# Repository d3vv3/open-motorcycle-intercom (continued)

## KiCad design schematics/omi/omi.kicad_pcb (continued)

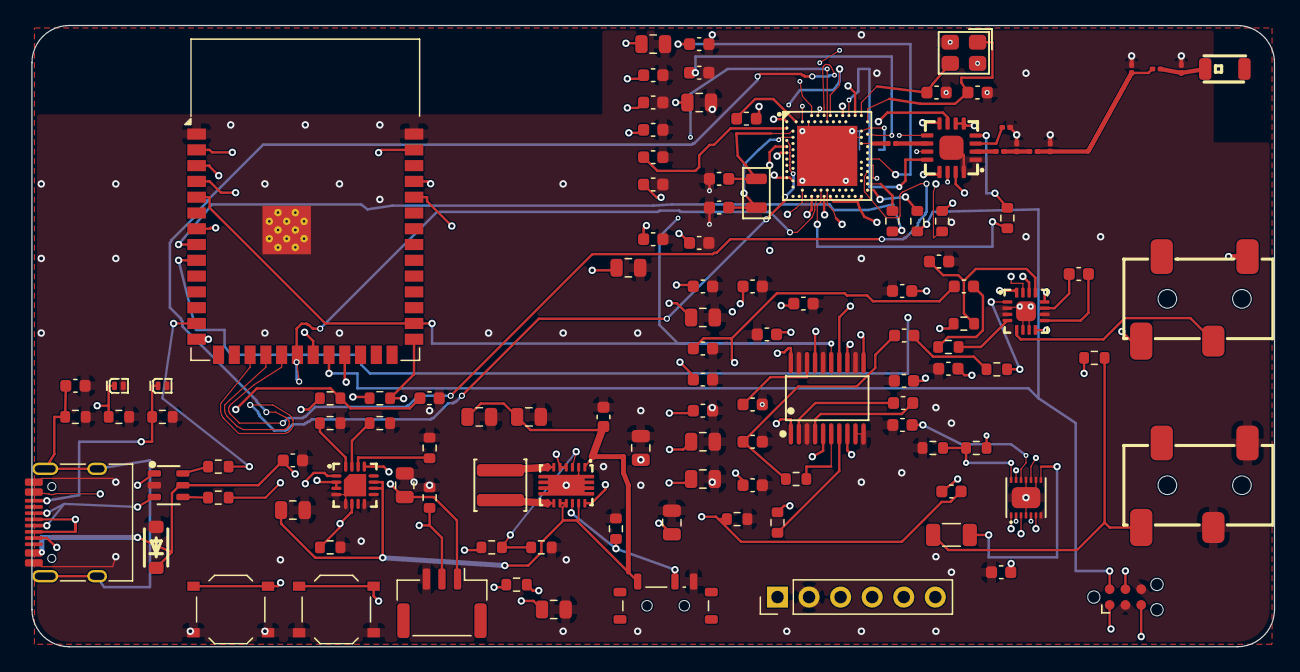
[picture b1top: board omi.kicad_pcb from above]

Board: 4 copper layers, 100.0 x 50.0 mm, 117 parts (1 on the bottom side), 99 nets.

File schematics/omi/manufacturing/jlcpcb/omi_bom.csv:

"Designator","Comment","Footprint","LCSC"
"AE1","2450AT18A100E","JLC-MCP:ANT-SMD_L3.2-W1.6","C89334"
"C23","4.7uF","Capacitor_SMD:C_0805_2012Metric","C76639"
"C24","100nF","Capacitor_SMD:C_0603_1608Metric","C108079"
"C25","100nF","Capacitor_SMD:C_0603_1608Metric","C108079"
"C26","100nF","Capacitor_SMD:C_0603_1608Metric","C108079"
"C27","100nF DEC1","Capacitor_SMD:C_0603_1608Metric","C108079"
"C28","100nF DEC2","Capacitor_SMD:C_0603_1608Metric","C108079"
"C29","100pF DEC3","Capacitor_SMD:C_0603_1608Metric","C14665"
"C30","1uF DEC4","Capacitor_SMD:C_0603_1608Metric","C113807"
"C31","1uF DEC5","Capacitor_SMD:C_0603_1608Metric","C113807"
"C32","1uF DEC6","Capacitor_SMD:C_0603_1608Metric","C113807"
"C33","4.7uF DECUSB","Capacitor_SMD:C_0805_2012Metric","C76639"
"C34","12pF","Capacitor_SMD:C_0603_1608Metric","C107034"
"C35","12pF","Capacitor_SMD:C_0603_1608Metric","C107034"
"C36","20pF","Capacitor_SMD:C_0603_1608Metric","C325469"
"C37","20pF","Capacitor_SMD:C_0603_1608Metric","C325469"
"C38","100nF","Capacitor_SMD:C_0603_1608Metric","C108079"
"C39","10uF","Capacitor_SMD:C_0805_2012Metric","C380331"
"C42","1uF","Capacitor_SMD:C_0603_1608Metric","C113807"
"C43","4.7uF","Capacitor_SMD:C_0805_2012Metric","C76639"
"C44","4.7uF","Capacitor_SMD:C_0805_2012Metric","C76639"
"C45","10uF 6.3V X5R","Capacitor_SMD:C_0805_2012Metric","C380331"
"C46","10uF 6.3V X5R","Capacitor_SMD:C_0805_2012Metric","C380331"
"C47","100nF","Capacitor_SMD:C_0603_1608Metric","C108079"
"C48","22uF 6.3V X5R","Capacitor_SMD:C_0805_2012Metric","C380336"
"C49","22uF 6.3V X5R","Capacitor_SMD:C_0805_2012Metric","C380336"
"C50","22uF 6.3V X5R","Capacitor_SMD:C_0805_2012Metric","C380336"
"C51","1uF","Capacitor_SMD:C_0603_1608Metric","C113807"
"C52","1.0pF C0G RF (Nordic ref)","Capacitor_SMD:C_0201_0603Metric","C85893"
"C53","2.0pF C0G RF (Nordic ref)","Capacitor_SMD:C_0201_0603Metric","C88875"
"C54","1.0pF C0G RF (Nordic ref)","Capacitor_SMD:C_0201_0603Metric","C85893"
"C55","100nF","Capacitor_SMD:C_0603_1608Metric","C108079"
"C56","10uF","Capacitor_SMD:C_0805_2012Metric","C380331"
"C57","100nF","Capacitor_SMD:C_0603_1608Metric","C108079"
"C58","10uF","Capacitor_SMD:C_0805_2012Metric","C380331"
"C59","100nF","Capacitor_SMD:C_0603_1608Metric","C108079"
"C60","10uF","Capacitor_SMD:C_0805_2012Metric","C380331"
"C61","2.2uF","Capacitor_SMD:C_0603_1608Metric","C513691"
"C62","2.2uF","Capacitor_SMD:C_0603_1608Metric","C513691"
"C63","100nF","Capacitor_SMD:C_0603_1608Metric","C108079"
"C64","2.2nF C0G","Capacitor_SMD:C_0603_1608Metric","C107043"
"C65","2.2nF C0G","Capacitor_SMD:C_0603_1608Metric","C107043"
"C66","1uF","Capacitor_SMD:C_0603_1608Metric","C113807"
"C67","1uF","Capacitor_SMD:C_0603_1608Metric","C113807"
"C68","1uF","Capacitor_SMD:C_0603_1608Metric","C113807"
"C69","1uF","Capacitor_SMD:C_0603_1608Metric","C113807"
"C70","2.2uF","Capacitor_SMD:C_0603_1608Metric","C513691"
"C71","2.2uF","Capacitor_SMD:C_0603_1608Metric","C513691"
"C72","100nF","Capacitor_SMD:C_0603_1608Metric","C108079"
"C73","100nF","Capacitor_SMD:C_0603_1608Metric","C108079"
"C74","1uF","Capacitor_SMD:C_0603_1608Metric","C113807"
"C75","470nF","Capacitor_SMD:C_0603_1608Metric","C1623"
"C76","2.2uF","Capacitor_SMD:C_0603_1608Metric","C513691"
"C77","68nF","Capacitor_SMD:C_0603_1608Metric","C107071"
"C78","100nF C0G","Capacitor_SMD:C_1206_3216Metric","C170182"
"C79","1uF","Capacitor_SMD:C_0603_1608Metric","C113807"
"D1","PESD5V0S1UL CC1","JLC-MCP:SOD-882_L1.0-W0.6-RD","C85402"
"D2","PESD5V0S1UL CC2","JLC-MCP:SOD-882_L1.0-W0.6-RD","C85402"
"D3","SMF5.0A VBUS TVS","JLC-MCP:SOD-123F_L2.8-W1.8-LS3.7-RD","C151296"
"J3","NRF SWD RECOVERY","Connector:Tag-Connect_TC2030-IDC-NL_2x03_P1.27mm_Vertical","Not stocked - factory fixture"
"J4","USB-C","Connector_USB:USB_C_Receptacle_HRO_TYPE-C-31-M-12","C165948"
"J5","LiPo + NTC","Connector_JST:JST_GH_BM03B-GHS-TBT_1x03-1MP_P1.25mm_Vertical","C161691"
"J6","PJ-327C-4A Headphones","JLC-MCP:AUDIO-SMD_PJ-327C-4A","C145813"
"J7","PJ-327C-4A Microphone","JLC-MCP:AUDIO-SMD_PJ-327C-4A","C145813"
"J8","ESP FACTORY","Connector_PinHeader_2.54mm:PinHeader_1x06_P2.54mm_Vertical","C492405"
"L1","10uH >=100mA","Inductor_SMD:L_0603_1608Metric","C713281"
"L2","XFL4020-152MEC 1.5uH","JLC-MCP:IND-SMD_L4.0-W4.0-A","C3033018"
"L3","1.9nH RF (Nordic ref)","Inductor_SMD:L_0201_0603Metric","C206445"
"L4","3.0nH RF (Nordic ref)","Inductor_SMD:L_0201_0603Metric","C98044"
"R12","0R antenna tune","Resistor_SMD:R_0201_0603Metric","C106228"
"R13","33R","Resistor_SMD:R_0603_1608Metric","C23140"
"R14","33R","Resistor_SMD:R_0603_1608Metric","C23140"
"R15","10k","Resistor_SMD:R_0603_1608Metric","C25804"
"R16","5.1k 1%","Resistor_SMD:R_0603_1608Metric","C23186"
"R17","5.1k 1%","Resistor_SMD:R_0603_1608Metric","C23186"
"R18","1.13k 1%","Resistor_SMD:R_0603_1608Metric","C22833"
"R19","4.12k 1%","Resistor_SMD:R_0603_1608Metric","C23041"
"R20","46.4k 1%","Resistor_SMD:R_0603_1608Metric","C23059"
"R22","1M 1%","Resistor_SMD:R_0603_1608Metric","C22935"
"R23","180k 1%","Resistor_SMD:R_0603_1608Metric","C22827"
"R24","1M","Resistor_SMD:R_0603_1608Metric","C22935"
"R25","10k","Resistor_SMD:R_0603_1608Metric","C25804"
"R26","10k","Resistor_SMD:R_0603_1608Metric","C25804"
"R27","49.9R 1% ANT2 termination","Resistor_SMD:R_0201_0603Metric","C155744"
"R28","33k FEM MODE","Resistor_SMD:R_0603_1608Metric","C4216"
"R29","470R","Resistor_SMD:R_0603_1608Metric","C23179"
"R30","470R","Resistor_SMD:R_0603_1608Metric","C23179"
"R31","18k","Resistor_SMD:R_0603_1608Metric","C25810"
"R32","18k","Resistor_SMD:R_0603_1608Metric","C25810"
"R33","100k","Resistor_SMD:R_0603_1608Metric","C25803"
"R34","150k","Resistor_SMD:R_0603_1608Metric","C22807"
"R35","100k","Resistor_SMD:R_0603_1608Metric","C25803"
"R36","2.2k","Resistor_SMD:R_0603_1608Metric","C4190"
"R37","100k","Resistor_SMD:R_0603_1608Metric","C25803"
"R38","22R USB D-","Resistor_SMD:R_0603_1608Metric","C23345"
"R39","22R USB D+","Resistor_SMD:R_0603_1608Metric","C23345"
"R40","100k USB100 default","Resistor_SMD:R_0603_1608Metric","C25803"
"R41","100k EN pulldown","Resistor_SMD:R_0603_1608Metric","C25803"
"R42","0R SHIELD BOND","Resistor_SMD:R_0603_1608Metric","C21189"
"SW1","ESP RESET","Button_Switch_SMD:SW_Push_1P1T_XKB_TS-1187A","C318884"
"SW2","ESP BOOT","Button_Switch_SMD:SW_Push_1P1T_XKB_TS-1187A","C318884"
"SW3","POWER ON/OFF","Button_Switch_SMD:SW_SPDT_Shouhan_MSK12C02","C431540"
"U1","ESP32-S3-WROOM-1","RF_Module:ESP32-S3-WROOM-1","C2913198"
"U2","NRF52840-QIAA-R","JLC-MCP:AQFN-73_L7.0-W7.0-P0.50-BL-EP4.8","C190794"
"U3","NRF21540-QDAA-R","JLC-MCP:QFN-16_L4.0-W4.0-P0.65-BL-EP2.7","C1518188"
"U4","BQ24074RGTR","JLC-MCP:QFN-16_L3.0-W3.0-P0.50-TL-EP1.7","C54313"
"U5","TPS63020DSJR","JLC-MCP:VSON-14_L4.0-W3.0-P0.50-BL-EP_TI_DSJ","C15483"
"U6","USBLC6-2SC6","JLC-MCP:SOT-23-6_L2.9-W1.6-P0.95-LS2.8-BL","C7519"
"U7","PCM5102APWR","JLC-MCP:TSSOP-20_L6.5-W4.4-P0.65-LS6.4-BL","C107671"
"U8","MAX9814ETD+T","JLC-MCP:TDFN-14_L3.0-W3.0-P0.40-BL-EP","C41714"
"U9","TPA6132A2RTER","JLC-MCP:WQFN-16_L3.0-W3.0-P0.50-TL-EP1.6","C69901"
"Y1","32MHz 8pF","JLC-MCP:CRYSTAL-SMD_4P-L3.2-W2.5-BL","C426985"
"Y2","32.768kHz 12.5pF","JLC-MCP:OSC-SMD_L3.2-W1.5","C97606"

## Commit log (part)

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2026-01-01 docs: Initial scope and considerations
2026-01-01 docs: Architecture breakdown in phases
2026-01-01 docs: Power estimations and targets
2026-01-01 docs: First protocol specification
2026-01-01 docs: Audio architecture
2026-01-01 docs: Inter MCU specification
2026-01-01 docs: TDMA design
2026-01-01 docs: Project timeline
2026-01-01 docs: Getting started for development
2026-01-01 chore: License
2026-01-22 feat: Phase 0
    Repository structure
    ESP-IDF + CMake
    Opus build integration
    Logging framework with timestamps
    Hardware selection
    Firmware skeleton
2026-01-22 feat(phase0): Initialization
    Repository structure
    ESP-IDF + CMake
    Opus build integration
    Logging framework with timestamps
    Hardware selection
    Firmware skeleton
2026-01-23 test(phase1): Hardware wiring
2026-01-23 docs(phase1): Hardware wiring
2026-01-23 feat(phase1): Audio bring-up
    VOX
    Opus
2026-01-23 feat(phase2): Mesh connectivity
    Mesh implementation
    Coordinator, participant roles
2026-01-23 fix: board2 serial hangs after reset
2026-01-24 feat(phase3): Collect power measurement
    Add connection and disconnection sounds
2026-01-24 docs(phase3): PCMA5102A wiring
2026-01-24 feat(phase4): Startup sound
2026-01-26 fix(phase4): High pitched mic playback
2026-01-26 fix(phase2): Use MAX9814 and decrease attenuation
2026-02-08 feat: Enable or disable mesh intercom
    Allows for saving battery when the mesh is not needed (solo rider).
    Will make more sense once bluetooth is in place.
2026-02-13 feat: Use and connect SPI for nRF52
2026-03-20 debug
2026-03-21 fix: bottleneck in nRF-ESP SPI
2026-03-21 feat: add RTT logs for debugging and baseline
2026-03-21 feat: noise and echo supression
2026-03-21 refactor: modularize jitter and audio
2026-03-21 fix: SPI 100ms poll stalls
2026-03-21 fix: sync filtering and decimation
2026-03-21 feat: OMI initial schematics
2026-03-22 docs: Update information and rename project
2026-03-22 fix: Missing protocol status, CRC and others
2026-03-22 fix: Dropped packages and underruns
2026-03-22 fix: Improve audio jitter and cuts
2026-03-23 feat: use clock sync between nRF and ESP
2026-03-23 fix: Opus PLC to fix robotic voice
2026-03-24 feat: 1Mbps link budget in ESB since drops come mainly from air tx
2026-03-24 feat: Ensure nRF52 mesh is disabled at startup
2026-03-24 feat: Update schematics for common xtal
2026-03-24 chore: Add benchmarking script
2026-03-24 chore: Exclude KiCad backups
2026-03-24 fix: LEAVE or LOST audio beep, switch to channel 40
2026-03-24 feat: Get rid of SPI drops
2026-03-24 revert: feat: Get rid of SPI drops
    This reverts commit 4f6dd60d8cc122c7aaff47bbf9811395b35bdb97.
2026-03-24 feat: Add pipeline latency logging
2026-03-24 feat: Add ACK signal between nRF52 and ESP32
2026-03-24 fix: Reduce latency by 20ms by smaller queues
2026-03-24 fix: Reconcile mesh if two coordinators, lowest mac wins
2026-03-25 fix: Increase transmission_power to 8dBm
    --- Quick Summary ---
    /dev/ttyACM1 (nRF): spi_gap=0.0% | rf_gap=0.52% | rf_delivery=99.78%
    /dev/ttyACM3 (nRF): spi_gap=0.39% | rf_gap=0.15% | rf_delivery=99.91%
    /dev/ttyACM4 (ESP): glitches=0 (0.0/min) | e2e_delivery=99.8% |
    e2e_gap=0.15%
    Latency: total avg=59ms max=82ms | TX avg=18.9ms max=38.0ms | RX
2026-03-26 feat: multi-hop and ESB 250kbps
    --- Quick Summary ---
    /dev/ttyACM2 (nRF): spi_gap=0.0% | rf_gap=0.17% | rf_delivery=99.63%
    /dev/ttyACM3 (nRF): spi_gap=0.0% | rf_gap=0.22% | rf_delivery=99.96%
    /dev/ttyACM4 (ESP): glitches=0 (0.0/min) | e2e_delivery=99.62% |
    e2e_gap=0.35%
    Latency: total avg=59ms max=79ms | TX avg=18.7ms max=28.5ms | RX
2026-03-26 fix: minor bugs from multi-hop
    --- Quick Summary ---
    /dev/ttyACM2 (nRF): spi_gap=0.0% | rf_gap=0.13% | rf_delivery=99.93%
    /dev/ttyACM3 (nRF): spi_gap=0.0% | rf_gap=0.25% | rf_delivery=99.75%
    /dev/ttyACM4 (ESP): glitches=0 (0.0/min) | e2e_delivery=99.67% |
    e2e_gap=0.3%
    Latency: total avg=59ms max=79ms | TX avg=18.8ms max=28.0ms | RX
2026-06-17 docs: Update project landing
2026-06-17 feat: per-peer timeout for ESB mesh
    Drop peers that go silent past MESH_NODE_TIMEOUT_MS (3s) via a 1 Hz
    check in status_work_handler, mirroring the ESP-NOW path. Liveness is
    refreshed by keepalive/status/audio/join, all independent of voice
    activity, so silence-suppressed nodes stay alive. Skips self and the
    coordinator (whose loss is handled by the SYNC_TIMEOUT re-election path).
2026-06-17 feat: suppress radio TX during silence via Opus DTX
    Enable Opus DTX and transmit only comfort-noise (SID) updates during
    VOX silence, dropping the 1-2 byte DTX frames so the radio goes quiet.
    Plumb the per-frame active flag end-to-end so the receiver treats DTX
    gaps as intentional silence (no false underrun/glitch counts) rather
    than packet loss; ESP-NOW defaults to active so its behavior is
    unchanged. Disable FORCE_TX_ALWAYS_FOR_TEST so gating engages.
2026-06-17 docs: conceal documentation with codebase development
2026-06-18 refactor: unify mesh wire protocol into one shared header
2026-06-18 refactor: guard speaker-grant state against timer/task data race
2026-06-18 docs: document nRF mesh-state concurrency invariant
    The nRF speaker-grant / peer state has no locks, but it is not racy: all
    access is confined to the system workqueue (rx/status/slot work run
    serially), and the ISR paths only k_work_submit. Document this invariant
    so future changes don't introduce a second context without adding
    synchronization (unlike the ESP-NOW build, which has a real timer/task
    split guarded by s_speaker_mux).
2026-06-28 docs: link discord
